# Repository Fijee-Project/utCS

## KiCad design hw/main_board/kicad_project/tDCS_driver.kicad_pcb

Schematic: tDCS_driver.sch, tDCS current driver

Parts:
P14, P15: CONN_5X2
P16: CONN_3X2
P17, P18: CONN_2X2
SCREW1, SCREW2, SCREW3, SCREW4: CONN_1

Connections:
/MUXC0: P14.9, P15.2; also elsewhere on the board
/MUXC1: P14.7, P15.4; also elsewhere on the board
/MUXC2: P14.5, P15.6; also elsewhere on the board
/MUXC3: P14.3, P15.8; also elsewhere on the board
/MUXC4: P14.1, P15.10; also elsewhere on the board
/MUXCOM0: P16.1, P16.6; also elsewhere on the board
/MUXCOM1: P16.3, P16.4; also elsewhere on the board
/MUXCOM2: P16.2, P16.5; also elsewhere on the board
/MUXD0: P14.10, P15.1; also elsewhere on the board
/MUXD1: P14.8, P15.3; also elsewhere on the board
/MUXD2: P14.6, P15.5; also elsewhere on the board
/MUXD3: P14.4, P15.7; also elsewhere on the board
/MUXD4: P14.2, P15.9; also elsewhere on the board
/powergen/MUXVSS: P18.1, P18.2; also elsewhere on the board
AGND: P17.1, P17.2, P17.3, P17.4; also elsewhere on the board
DVDD_2V5: P18.3, P18.4; also elsewhere on the board

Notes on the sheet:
A0-4 for the input/output mux boards

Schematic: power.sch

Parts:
P4: CONN_3X2

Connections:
/powergen/MUXVSS: P4.2; also elsewhere on the board
AGND: P4.4; also elsewhere on the board
AVDD: P4.5; also elsewhere on the board
AVSS: P4.6; also elsewhere on the board
DVDD_2V5: P4.1; also elsewhere on the board

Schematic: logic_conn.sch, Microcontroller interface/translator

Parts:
C37, C38, C41, C42: 0.1uF; 0603
P6: CONN_25X2
U8, U9: MAX3002; TSSOP_20

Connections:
/Clock/CLK_TWI0: P6.1; also elsewhere on the board
/Clock/CLK_TWI1: P6.2; also elsewhere on the board
/CurrentSource/GAIN_BUS0: P6.14; also elsewhere on the board
/CurrentSource/GAIN_BUS1: P6.10; also elsewhere on the board
/CurrentSource/GAIN_BUS2: P6.11; also elsewhere on the board
/CurrentSource/GAIN_BUS3: P6.12; also elsewhere on the board
/CurrentSource/GAIN_BUS4: P6.13; also elsewhere on the board
/CurrentSource/RNG_0: P6.23; also elsewhere on the board
/CurrentSource/RNG_1: P6.22; also elsewhere on the board
/CurrentSource/RNG_2: P6.21; also elsewhere on the board
/CurrentSource/RNG_3: P6.20; also elsewhere on the board
/DDS/DDS_BUS0: P6.7; also elsewhere on the board
/DDS/DDS_BUS1: P6.8; also elsewhere on the board
/DDS/DDS_BUS2: P6.9; also elsewhere on the board
/DDS/DDS_BUS3: P6.3; also elsewhere on the board
/DDS/DDS_BUS4: P6.4; also elsewhere on the board
/DDS/DDS_BUS5: P6.5; also elsewhere on the board
/DDS/DDS_BUS6: P6.6; also elsewhere on the board
/LogicTranslators/IN_MUX0: P6.26; also elsewhere on the board
/LogicTranslators/IN_MUX1: P6.27; also elsewhere on the board
/LogicTranslators/IN_MUX2: P6.24; also elsewhere on the board
/LogicTranslators/IN_MUX3: P6.25; also elsewhere on the board
/LogicTranslators/OUT_MUX0: P6.36; also elsewhere on the board
/LogicTranslators/OUT_MUX1: P6.37; also elsewhere on the board
/LogicTranslators/OUT_MUX2: P6.38; also elsewhere on the board
/LogicTranslators/OUT_MUX3: P6.39; also elsewhere on the board
/LogicTranslators/UCOUT14: P6.15, U8.20 (io-Vcc1)
/LogicTranslators/UCOUT15: P6.16, U8.18 (io-Vcc2)
/LogicTranslators/UCOUT16: P6.17, U8.17 (io-Vcc3)
/LogicTranslators/UCOUT17: P6.18, U8.16 (io-Vcc4)
/LogicTranslators/UCOUT18: P6.19, U8.15 (io-Vcc5)
/LogicTranslators/UCOUT27: P6.28, U9.20 (io-Vcc1)
/LogicTranslators/UCOUT28: P6.29, U9.18 (io-Vcc2)
/LogicTranslators/UCOUT29: P6.30, U9.17 (io-Vcc3)
/LogicTranslators/UCOUT30: P6.31, U9.16 (io-Vcc4)
/LogicTranslators/UCOUT31: P6.32, U9.15 (io-Vcc5)
/LogicTranslators/UCOUT32: P6.33, U9.14 (io-Vcc6)
/LogicTranslators/UCOUT33: P6.34, U9.13 (io-Vcc7)
/LogicTranslators/UCOUT34: P6.35, U9.12 (io-Vcc8)
/LogicTranslators/UCOUT39: P6.40
/LogicTranslators/UCOUT40: P6.41
/LogicTranslators/UCOUT41: P6.42
/LogicTranslators/UCOUT42: P6.43
/LogicTranslators/UCOUT43: P6.44
/LogicTranslators/UCOUT44: P6.45
/LogicTranslators/UCOUT45: P6.46
/LogicTranslators/UCOUT46: P6.47
/LogicTranslators/UCOUT47: P6.48
/LogicTranslators/UCOUT48: P6.49
/LogicTranslators/UCOUT49: P6.50
/MUXC0: U9.6 (io-Vl5); also elsewhere on the board
/MUXC1: U9.5 (io-Vl4); also elsewhere on the board
/MUXC2: U9.4 (io-Vl3); also elsewhere on the board
/MUXC3: U9.3 (io-Vl2); also elsewhere on the board
/MUXC4: U9.1 (io-Vl1); also elsewhere on the board
/MUXCOM0: U9.7 (io-Vl6); also elsewhere on the board
/MUXCOM1: U9.9 (io-Vl8); also elsewhere on the board
/MUXCOM2: U9.8 (io-Vl7); also elsewhere on the board
/MUXD0: U8.1 (io-Vl1); also elsewhere on the board
/MUXD1: U8.3 (io-Vl2); also elsewhere on the board
/MUXD2: U8.4 (io-Vl3); also elsewhere on the board
/MUXD3: U8.5 (io-Vl4); also elsewhere on the board
/MUXD4: U8.6 (io-Vl5); also elsewhere on the board
AGND: C37.2, C38.2, C41.2, C42.2, U9.11 (GND); also elsewhere on the board
DVDD_2V5: C37.1, C38.1, U8.2 (Vl), U9.2 (Vl); also elsewhere on the board

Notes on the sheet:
Does not need 2wire pullups, pulldowns needed for default on sleep/pselect/fselect (bit 6,7,9)

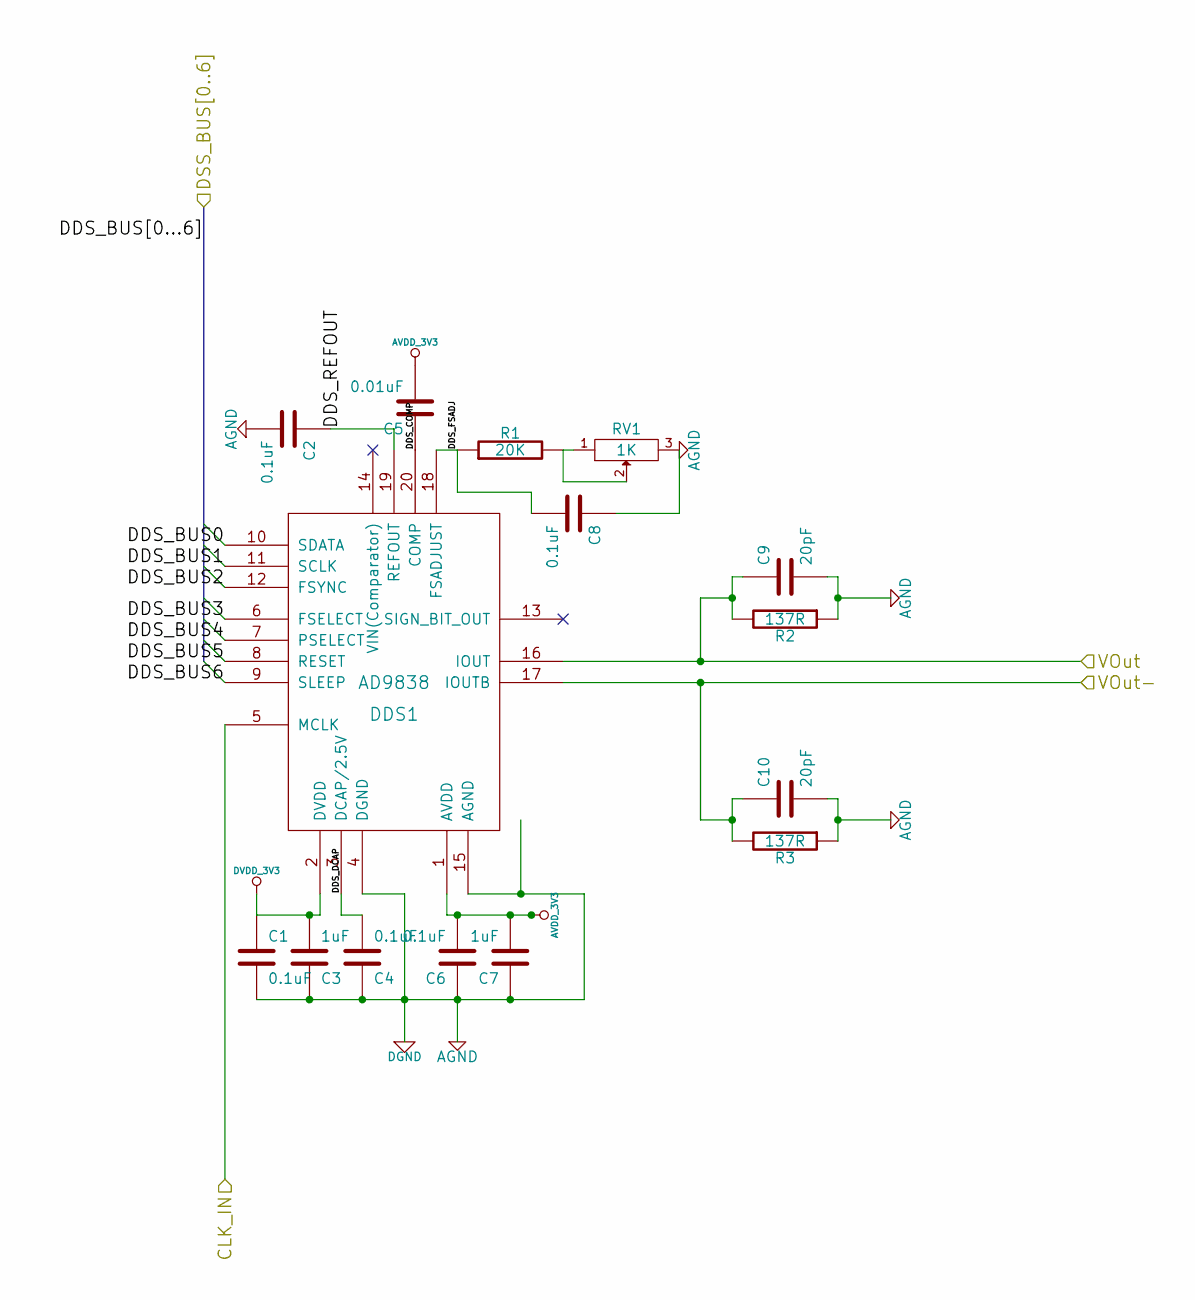
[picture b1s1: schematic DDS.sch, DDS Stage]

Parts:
C1, C2, C4, C6, C8: 0.1uF; 0603
C3, C7: 1uF; 0603
C5: 0.01uF; 0603
C9, C10: 20pF; 0603
DDS1: AD9838; LFCSP20_WQ
R1: 20K; 0603
R2, R3: 137R; 0603
RV1: 1K; 3224X

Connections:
/DDS/CLK_IN: DDS1.5 (MCLK); also elsewhere on the board
/DDS/DDS_BUS0: DDS1.10 (SDATA); also elsewhere on the board
/DDS/DDS_BUS1: DDS1.11 (SCLK); also elsewhere on the board
/DDS/DDS_BUS2: DDS1.12 (FSYNC); also elsewhere on the board
/DDS/DDS_BUS3: DDS1.6 (FSELECT); also elsewhere on the board
/DDS/DDS_BUS4: DDS1.7 (PSELECT); also elsewhere on the board
/DDS/DDS_BUS5: DDS1.8 (RESET); also elsewhere on the board
/DDS/DDS_BUS6: DDS1.9 (SLEEP); also elsewhere on the board
/DDS/DDS_COMP: C5.1, DDS1.20 (COMP)
/DDS/DDS_DCAP: C4.2, DDS1.3 (DCAP/2.5V)
/DDS/DDS_FSADJ: C8.2, DDS1.18 (FSADJUST), R1.1
/DDS/DDS_REFOUT: C2.1, DDS1.19 (REFOUT)
/DDS/VOut: C9.1, DDS1.16 (IOUT), R2.2; also elsewhere on the board
/DDS/VOut-: C10.1, DDS1.17 (IOUTB), R3.2; also elsewhere on the board
AGND: C1.2, C2.2, C3.1, C4.1, C6.1, C7.1, C8.1, C9.2, C10.2, DDS1.4 (DGND), DDS1.15 (AGND), DDS1.EP, R2.1, R3.1, RV1.3; also elsewhere on the board
unnamed: R1.2, RV1.1, RV1.2

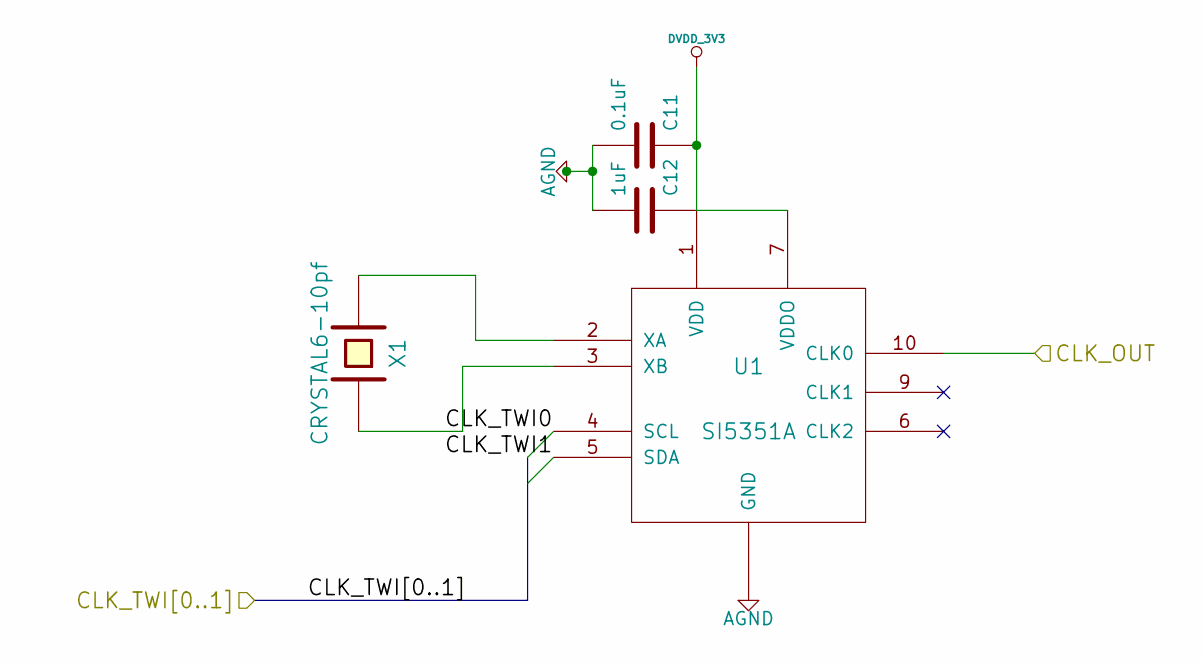
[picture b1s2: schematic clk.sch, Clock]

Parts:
C11: 0.1uF; 0603
C12: 1uF; 0603
U1: SI5351A; QSOP_16
X1: CRYSTAL6-10pf; ECX_53B

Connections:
/Clock/CLK_TWI0: U1.4 (SCL); also elsewhere on the board
/Clock/CLK_TWI1: U1.5 (SDA); also elsewhere on the board
/DDS/CLK_IN: U1.10 (CLK0); also elsewhere on the board
AGND: C11.2, C12.2, U1.8, U1.~ (GND); also elsewhere on the board
unnamed: U1.2 (XA), X1.2
unnamed: U1.3 (XB), X1.1

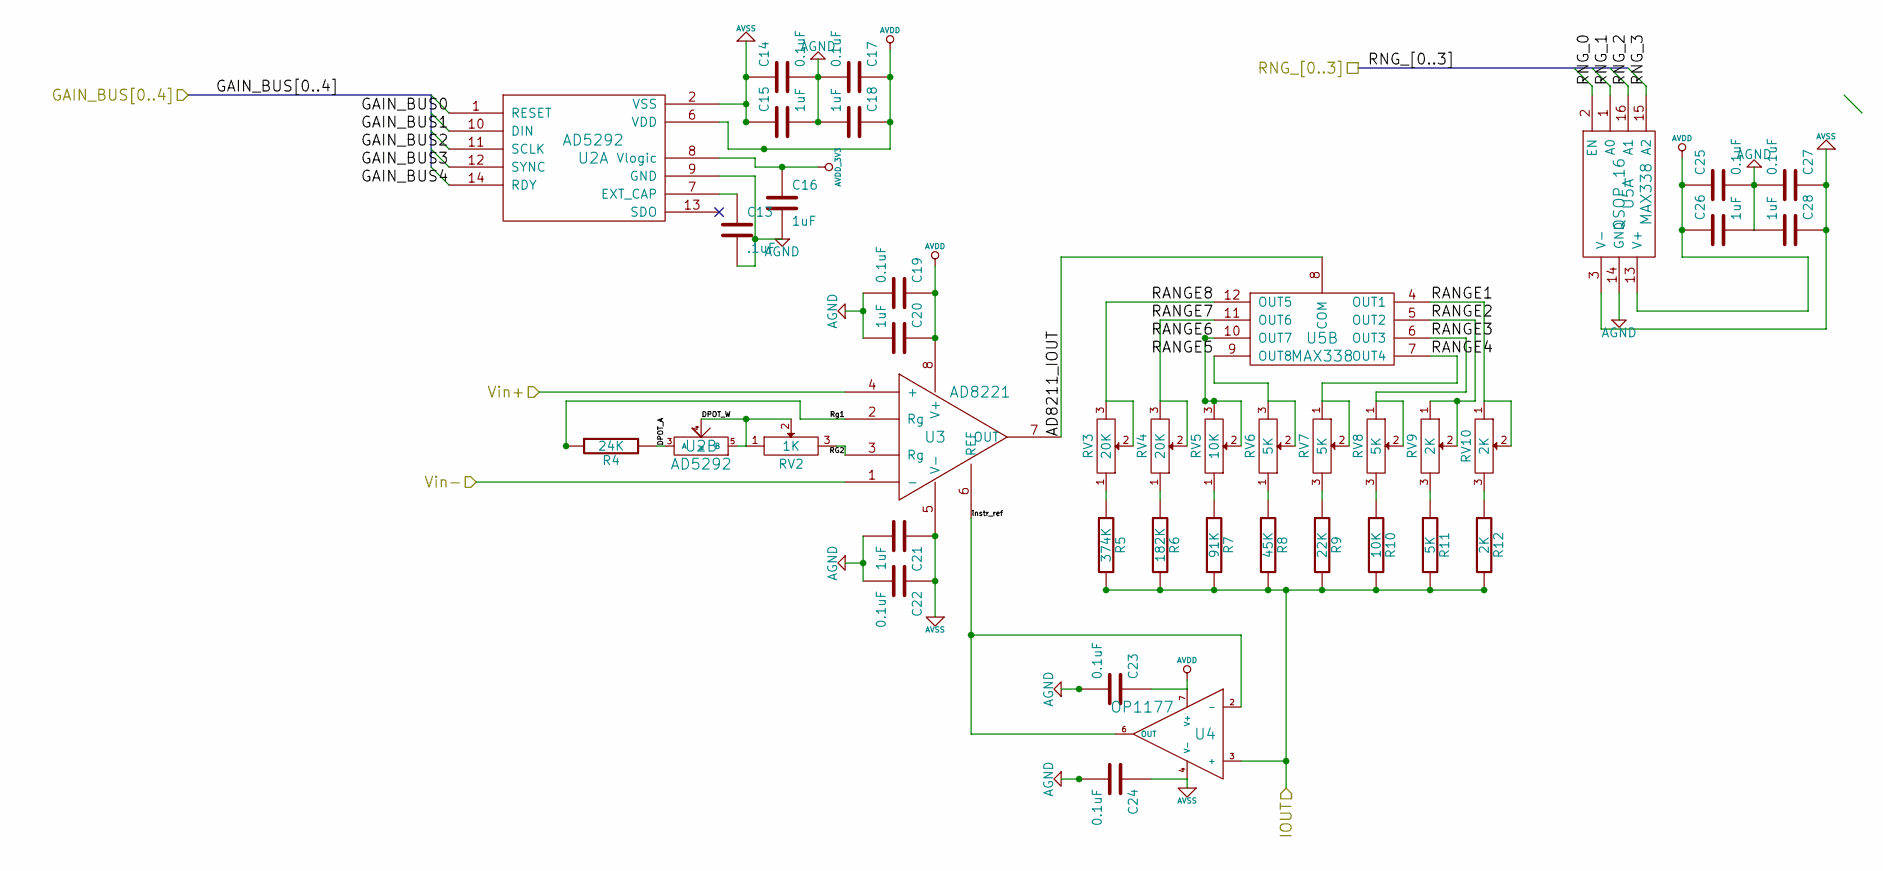
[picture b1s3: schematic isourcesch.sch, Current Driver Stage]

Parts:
C13: .1uF; 0603
C14, C17, C19, C22, C23, C24, C25, C27: 0.1uF; 0603
C15, C16, C18, C20, C21, C26, C28: 1uF; 0603
R4: 24K; 0603
R5: 374K; 0603
R6: 182K; 0603
R7: 91K; 0603
R8: 45K; 0603
R9: 22K; 0603
R10: 10K; 0603
R11: 5K; 0603
R12: 2K; 0603
RV2: 1K; 3224X
RV3, RV4: 20K; 3224X
RV5: 10K; 3224X
RV6, RV7, RV8: 5K; 3224X
RV9, RV10: 2K; 3224X
U2: AD5292; MSOP-10
U3: AD8221; TSSOP_14
U4: OP1177; MSOP_8
U5: MAX338; QSOP_16

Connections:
/CurrentSource/AD8211_IOUT: U3.7 (OUT), U5.8 (COM)
/CurrentSource/DPOT_A: R4.2, U2.3 (A)
/CurrentSource/DPOT_W: RV2.1, RV2.2, U2.4 (W), U2.5 (B)
/CurrentSource/GAIN_BUS0: U2.1 (RESET); also elsewhere on the board
/CurrentSource/GAIN_BUS1: U2.10 (DIN); also elsewhere on the board
/CurrentSource/GAIN_BUS2: U2.11 (SCLK); also elsewhere on the board
/CurrentSource/GAIN_BUS3: U2.12 (SYNC); also elsewhere on the board
/CurrentSource/GAIN_BUS4: U2.14 (RDY); also elsewhere on the board
/CurrentSource/IOUT: R5.2, R6.2, R7.2, R8.2, R9.2, R10.2, R11.2, R12.2, U4.3 (+); also elsewhere on the board
/CurrentSource/RANGE1: RV10.1, RV10.2, U5.4 (OUT1)
/CurrentSource/RANGE2: RV9.1, RV9.2, U5.5 (OUT2)
/CurrentSource/RANGE3: RV8.1, RV8.2, U5.6 (OUT3)
/CurrentSource/RANGE4: RV7.1, RV7.2, U5.7 (OUT4)
/CurrentSource/RANGE5: RV6.2, RV6.3, U5.9 (OUT8)
/CurrentSource/RANGE6: RV5.2, RV5.3, U5.10 (OUT7)
/CurrentSource/RANGE7: RV4.2, RV4.3, U5.11 (OUT6)
/CurrentSource/RANGE8: RV3.2, RV3.3, U5.12 (OUT5)
/CurrentSource/RG2: RV2.3, U3.3 (Rg)
/CurrentSource/RNG_0: U5.2 (EN); also elsewhere on the board
/CurrentSource/RNG_1: U5.1 (A0); also elsewhere on the board
/CurrentSource/RNG_2: U5.16 (A1); also elsewhere on the board
/CurrentSource/RNG_3: U5.15 (A2); also elsewhere on the board
/CurrentSource/Rg1: R4.1, U3.2 (Rg)
/CurrentSource/instr_ref: U3.6 (REF), U4.2 (-), U4.6 (OUT)
/DDS/VOut: U3.4 (+); also elsewhere on the board
/DDS/VOut-: U3.1 (-); also elsewhere on the board
AGND: C13.2, C14.2, C15.2, C16.2, C17.2, C18.2, C19.2, C20.2, C21.2, C22.2, C23.2, C24.2, C25.2, C26.2, C27.2, C28.2, U2.9 (GND), U5.14 (GND); also elsewhere on the board
AVDD: C17.1, C18.1, C19.1, C20.1, C23.1, C25.1, C26.1, U2.6 (VDD), U3.8 (V+), U4.7 (V+), U5.13 (V+); also elsewhere on the board
AVSS: C14.1, C15.1, C21.1, C22.1, C24.1, C27.1, C28.1, U2.2 (VSS), U3.5 (V-), U4.4 (V-), U5.3 (V-); also elsewhere on the board
unnamed: R9.1, RV7.3
unnamed: R8.1, RV6.1
unnamed: R7.1, RV5.1
unnamed: R6.1, RV4.1
unnamed: R11.1, RV9.3
unnamed: R12.1, RV10.3
unnamed: R10.1, RV8.3
unnamed: C13.1, U2.7 (EXT_CAP)
unnamed: R5.1, RV3.1

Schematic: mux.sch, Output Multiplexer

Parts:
C29, C31, C33, C43: 0.1uF; 0603
C30, C32, C34, C44: 1uF; 0603
P5, P7, P8, P9, P10, P11, P12, P13: CONN_2
U6, U7: MAX338; QSOP_16

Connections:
/CurrentSource/IOUT: U6.8 (COM); also elsewhere on the board
/LogicTranslators/IN_MUX0: U6.2 (EN); also elsewhere on the board
/LogicTranslators/IN_MUX1: U6.1 (A0); also elsewhere on the board
/LogicTranslators/IN_MUX2: U6.16 (A1); also elsewhere on the board
/LogicTranslators/IN_MUX3: U6.15 (A2); also elsewhere on the board
/LogicTranslators/OUT_MUX0: U7.2 (EN); also elsewhere on the board
/LogicTranslators/OUT_MUX1: U7.1 (A0); also elsewhere on the board
/LogicTranslators/OUT_MUX2: U7.16 (A1); also elsewhere on the board
/LogicTranslators/OUT_MUX3: U7.15 (A2); also elsewhere on the board
/OutputMultiplexer/MUXA0: P5.1, U6.4 (OUT1)
/OutputMultiplexer/MUXA1: P7.1, U6.5 (OUT2)
/OutputMultiplexer/MUXA2: P9.1, U6.6 (OUT3)
/OutputMultiplexer/MUXA3: P10.1, U6.7 (OUT4)
/OutputMultiplexer/MUXA4: P11.2, U6.12 (OUT5)
/OutputMultiplexer/MUXA5: P12.2, U6.11 (OUT6)
/OutputMultiplexer/MUXA6: P8.2, U6.10 (OUT7)
/OutputMultiplexer/MUXA7: P13.2, U6.9 (OUT8)
/OutputMultiplexer/MUXB0: P5.2, U7.7 (OUT4)
/OutputMultiplexer/MUXB1: P7.2, U7.6 (OUT3)
/OutputMultiplexer/MUXB2: P9.2, U7.5 (OUT2)
/OutputMultiplexer/MUXB3: P10.2, U7.4 (OUT1)
/OutputMultiplexer/MUXB4: P11.1, U7.9 (OUT8)
/OutputMultiplexer/MUXB5: P12.1, U7.10 (OUT7)
/OutputMultiplexer/MUXB6: P8.1, U7.11 (OUT6)
/OutputMultiplexer/MUXB7: P13.1, U7.12 (OUT5)
AGND: C29.2, C30.2, C31.2, C32.2, C33.2, C34.2, C43.2, C44.2, U6.14 (GND), U7.8 (COM), U7.14 (GND); also elsewhere on the board
AVDD: C29.1, C30.1, C33.1, C34.1, U6.13 (V+), U7.13 (V+); also elsewhere on the board
AVSS: C31.1, C32.1, C43.1, C44.1, U6.3 (V-), U7.3 (V-); also elsewhere on the board

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
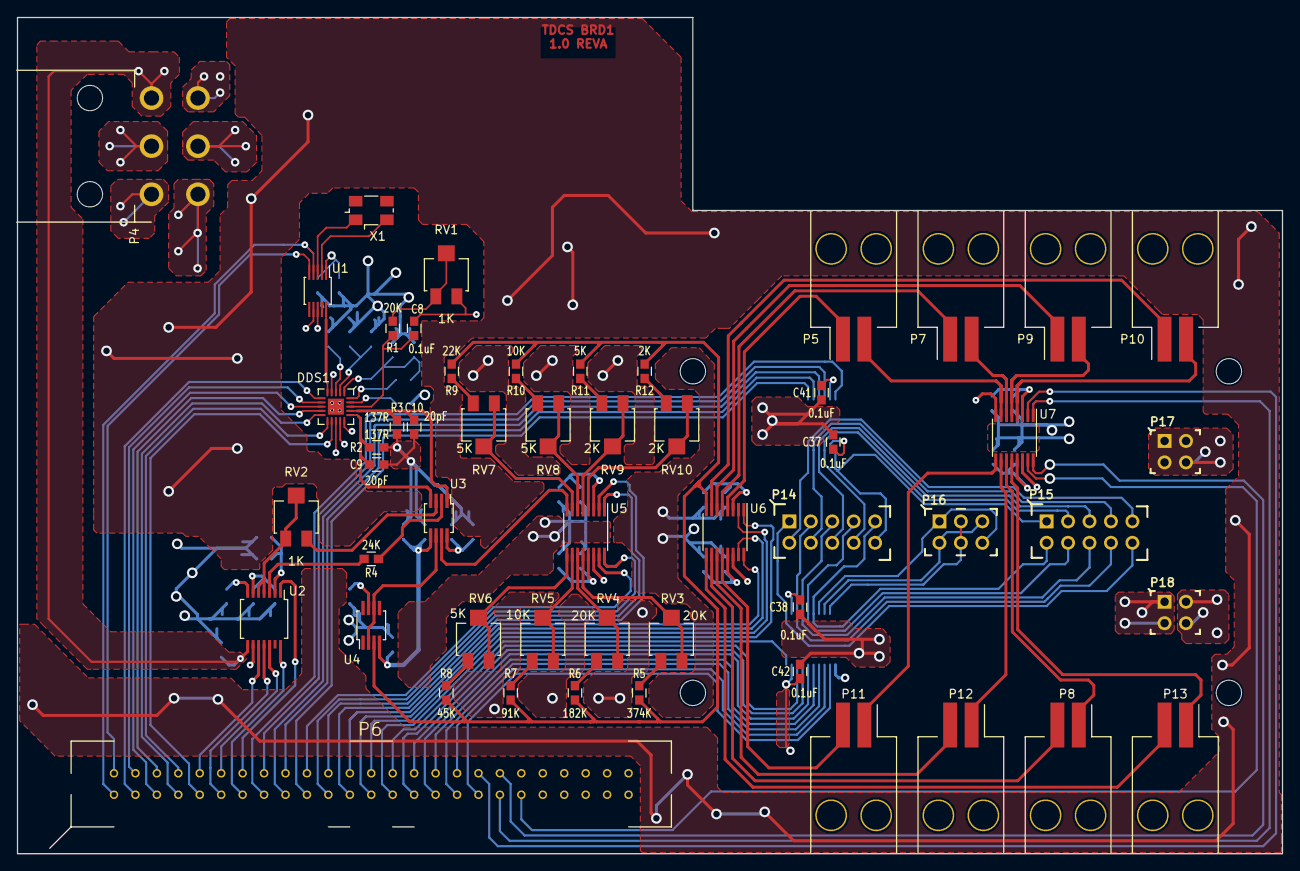
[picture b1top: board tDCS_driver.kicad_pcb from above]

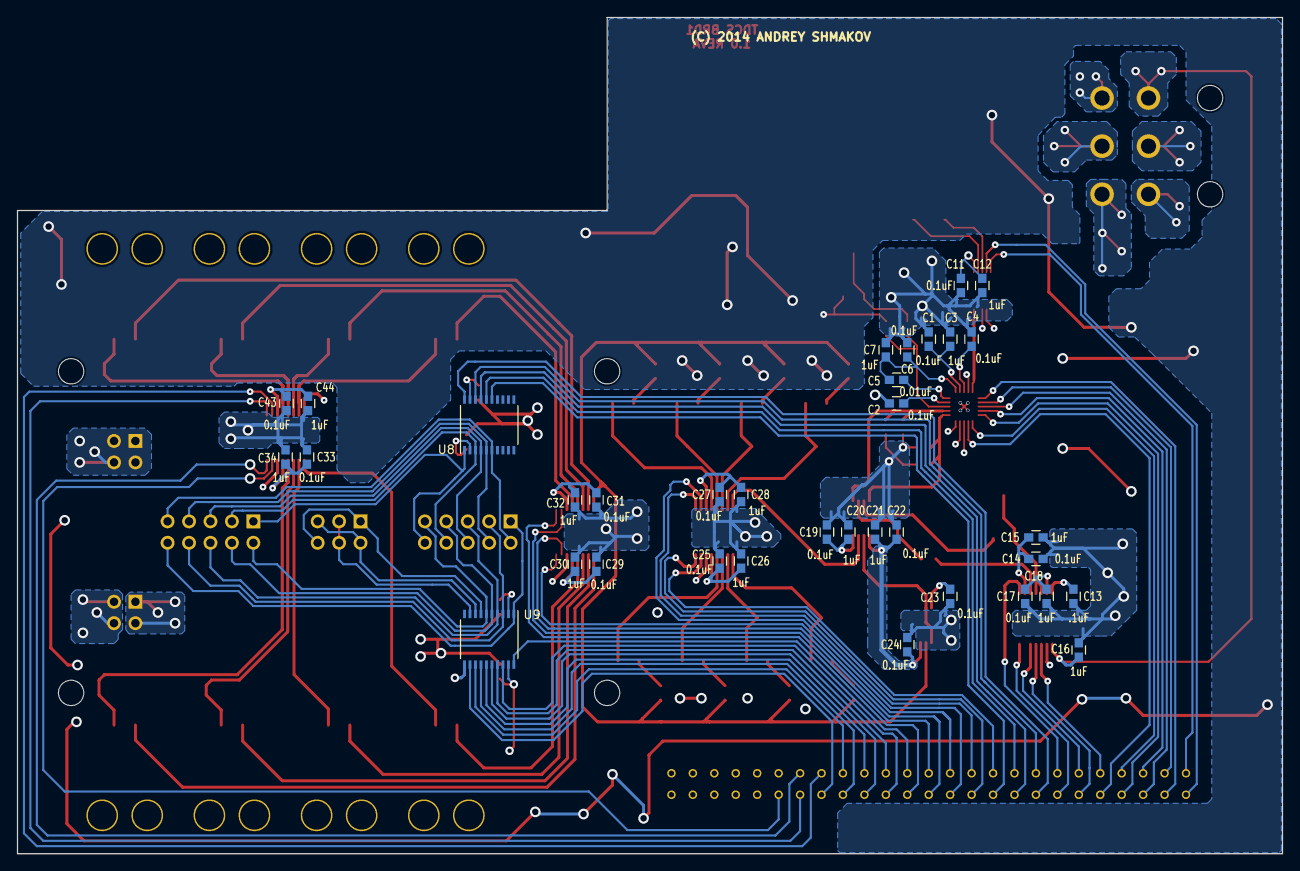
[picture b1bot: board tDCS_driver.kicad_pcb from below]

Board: 4 copper layers, 149.9 x 99.1 mm, 92 parts (35 on the bottom side), 108 nets.

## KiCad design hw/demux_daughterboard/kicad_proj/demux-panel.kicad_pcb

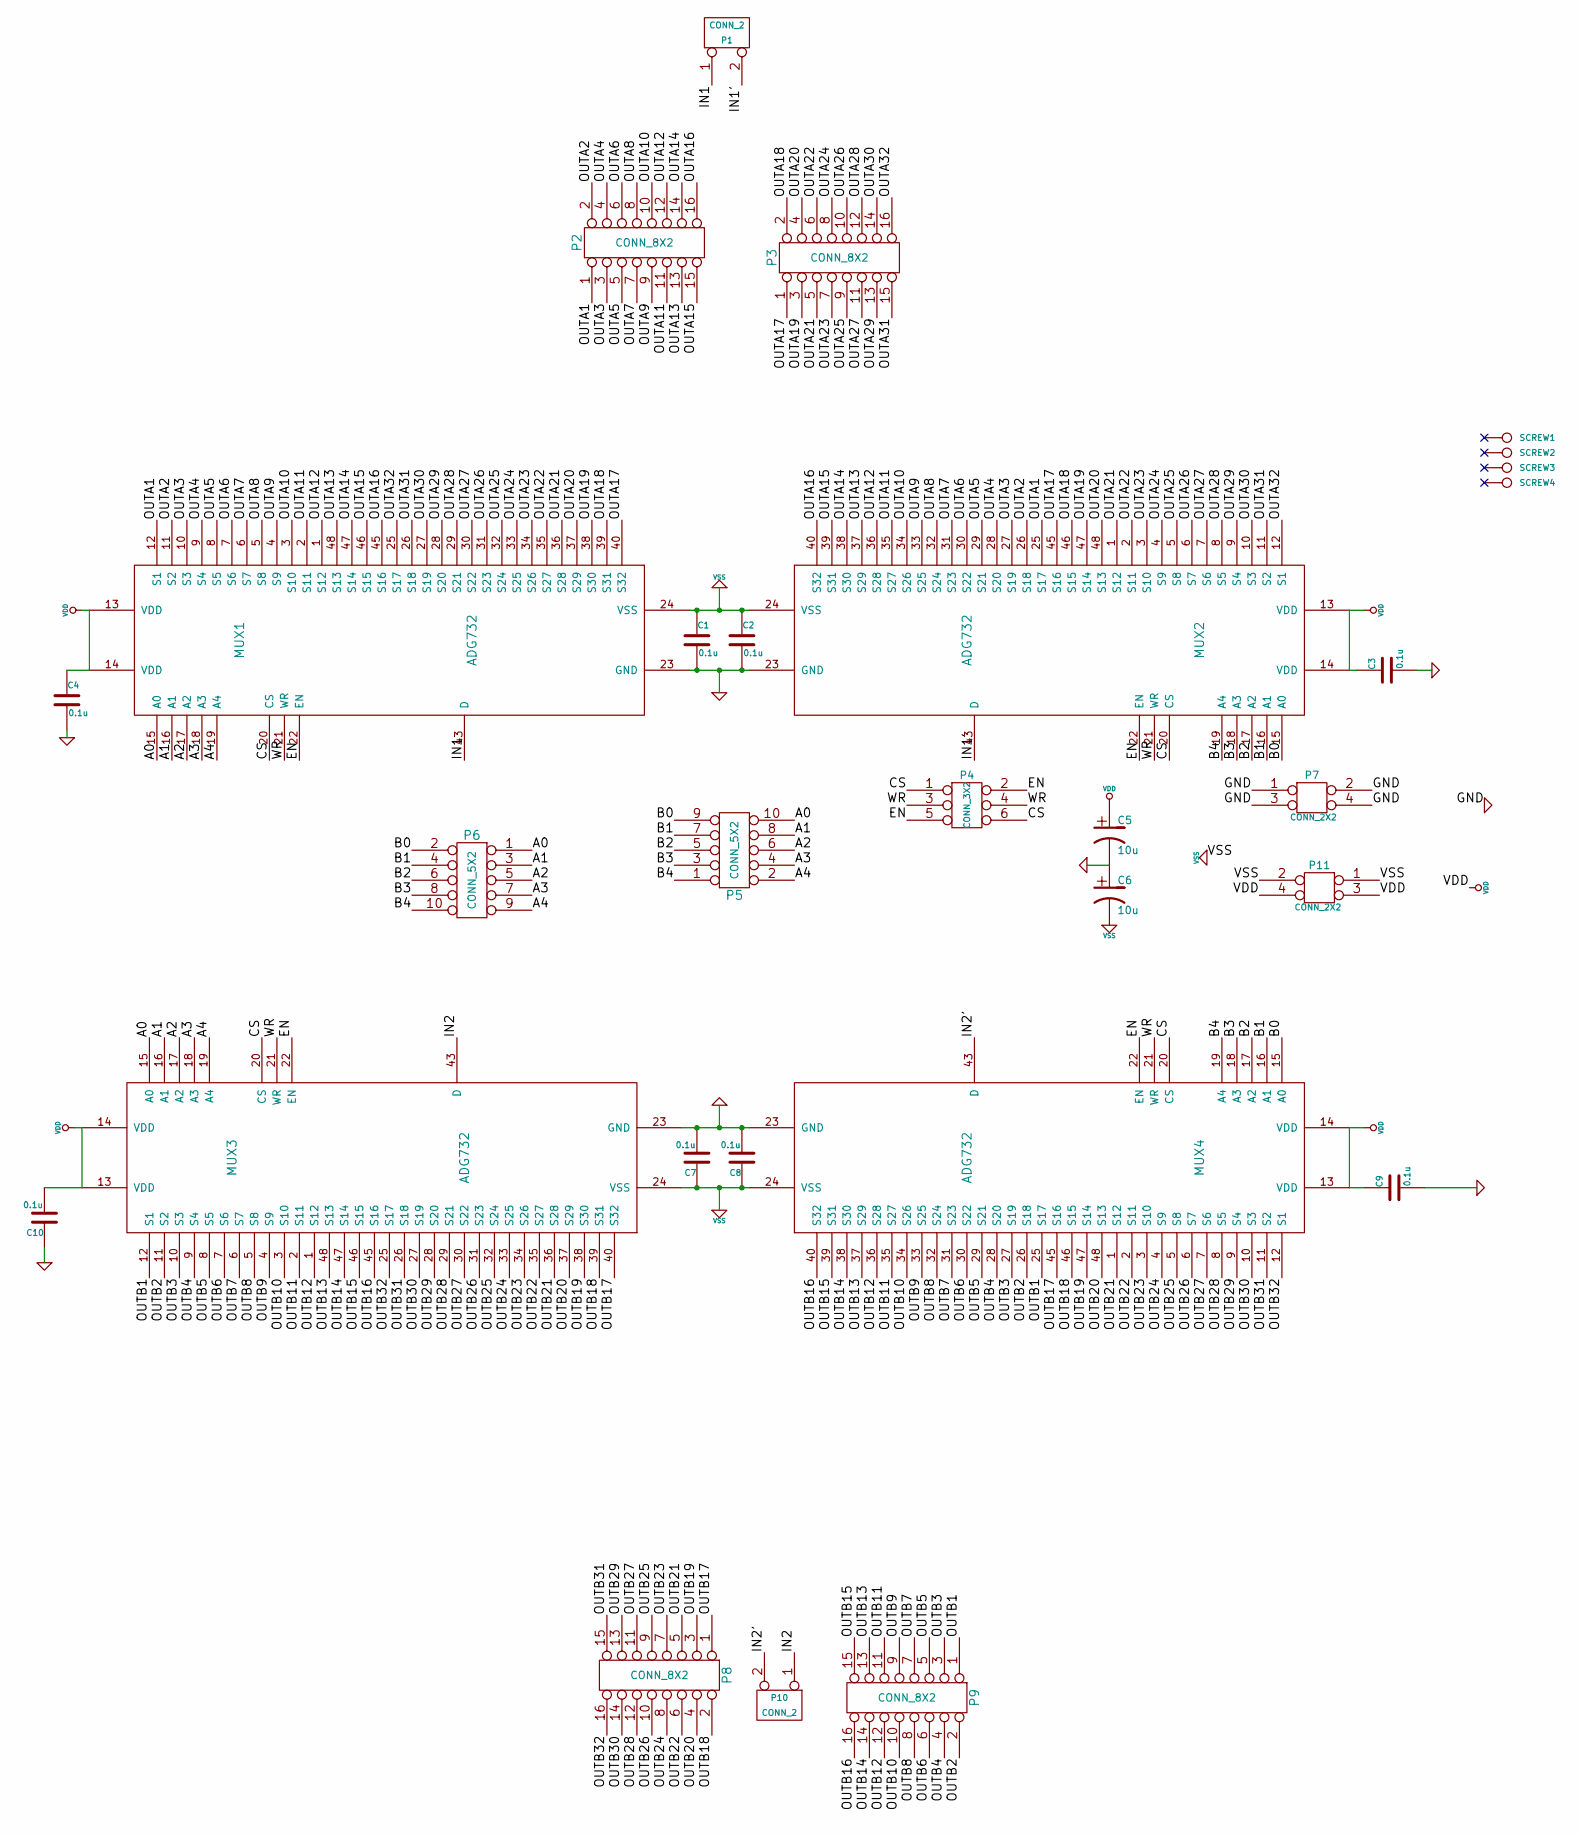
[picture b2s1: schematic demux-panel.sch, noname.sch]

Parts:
C1, C2, C3, C4, C7, C8, C9, C10: 0.1u
C5, C6: 10u
MUX1, MUX2, MUX3, MUX4: ADG732
P1, P10: CONN_2
P2, P3, P8, P9: CONN_8X2
P4: CONN_3X2
P5, P6: CONN_5X2
P7, P11: CONN_2X2
SCREW1, SCREW2, SCREW3, SCREW4: CONN_1

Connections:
/A0: MUX1.15 (A0), MUX3.15 (A0), P5.10, P6.1
/A1: MUX1.16 (A1), MUX3.16 (A1), P5.8, P6.3
/A2: MUX1.17 (A2), MUX3.17 (A2), P5.6, P6.5
/A3: MUX1.18 (A3), MUX3.18 (A3), P5.4, P6.7
/A4: MUX1.19 (A4), MUX3.19 (A4), P5.2, P6.9
/B0: MUX2.15 (A0), MUX4.15 (A0), P5.9, P6.2
/B1: MUX2.16 (A1), MUX4.16 (A1), P5.7, P6.4
/B2: MUX2.17 (A2), MUX4.17 (A2), P5.5, P6.6
/B3: MUX2.18 (A3), MUX4.18 (A3), P5.3, P6.8
/B4: MUX2.19 (A4), MUX4.19 (A4), P5.1, P6.10
/CS: MUX1.20 (CS), MUX2.20 (CS), MUX3.20 (CS), MUX4.20 (CS), P4.1, P4.6
/EN: MUX1.22 (EN), MUX2.22 (EN), MUX3.22 (EN), MUX4.22 (EN), P4.2, P4.5
/IN1: MUX1.43 (D), P1.1
/IN1': MUX2.43 (D), P1.2 (PM)
/IN2: MUX3.43 (D), P10.1
/IN2': MUX4.43 (D), P10.2 (PM)
/OUTA1: MUX1.12 (S1), MUX2.25 (S17), P2.1
/OUTA2: MUX1.11 (S2), MUX2.26 (S18), P2.2
/OUTA3: MUX1.10 (S3), MUX2.27 (S19), P2.3
/OUTA4: MUX1.9 (S4), MUX2.28 (S20), P2.4
/OUTA5: MUX1.8 (S5), MUX2.29 (S21), P2.5
/OUTA6: MUX1.7 (S6), MUX2.30 (S22), P2.6
/OUTA7: MUX1.6 (S7), MUX2.31 (S23), P2.7
/OUTA8: MUX1.5 (S8), MUX2.32 (S24), P2.8
/OUTA9: MUX1.4 (S9), MUX2.33 (S25), P2.9
/OUTA10: MUX1.3 (S10), MUX2.34 (S26), P2.10
/OUTA11: MUX1.2 (S11), MUX2.35 (S27), P2.11
/OUTA12: MUX1.1 (S12), MUX2.36 (S28), P2.12
/OUTA13: MUX1.48 (S13), MUX2.37 (S29), P2.13
/OUTA14: MUX1.47 (S14), MUX2.38 (S30), P2.14
/OUTA15: MUX1.46 (S15), MUX2.39 (S31), P2.15
/OUTA16: MUX1.45 (S16), MUX2.40 (S32), P2.16
/OUTA17: MUX1.40 (S32), MUX2.45 (S16), P3.1
/OUTA18: MUX1.39 (S31), MUX2.46 (S15), P3.2
/OUTA19: MUX1.38 (S30), MUX2.47 (S14), P3.3
/OUTA20: MUX1.37 (S29), MUX2.48 (S13), P3.4
/OUTA21: MUX1.36 (S28), MUX2.1 (S12), P3.5
/OUTA22: MUX1.35 (S27), MUX2.2 (S11), P3.6
/OUTA23: MUX1.34 (S26), MUX2.3 (S10), P3.7
/OUTA24: MUX1.33 (S25), MUX2.4 (S9), P3.8
/OUTA25: MUX1.32 (S24), MUX2.5 (S8), P3.9
/OUTA26: MUX1.31 (S23), MUX2.6 (S7), P3.10
/OUTA27: MUX1.30 (S22), MUX2.7 (S6), P3.11
/OUTA28: MUX1.29 (S21), MUX2.8 (S5), P3.12
/OUTA29: MUX1.28 (S20), MUX2.9 (S4), P3.13
/OUTA30: MUX1.27 (S19), MUX2.10 (S3), P3.14
/OUTA31: MUX1.26 (S18), MUX2.11 (S2), P3.15
/OUTA32: MUX1.25 (S17), MUX2.12 (S1), P3.16
/OUTB1: MUX3.12 (S1), MUX4.25 (S17), P9.1
/OUTB2: MUX3.11 (S2), MUX4.26 (S18), P9.2
/OUTB3: MUX3.10 (S3), MUX4.27 (S19), P9.3
/OUTB4: MUX3.9 (S4), MUX4.28 (S20), P9.4
/OUTB5: MUX3.8 (S5), MUX4.29 (S21), P9.5
/OUTB6: MUX3.7 (S6), MUX4.30 (S22), P9.6
/OUTB7: MUX3.6 (S7), MUX4.31 (S23), P9.7
/OUTB8: MUX3.5 (S8), MUX4.32 (S24), P9.8
/OUTB9: MUX3.4 (S9), MUX4.33 (S25), P9.9
/OUTB10: MUX3.3 (S10), MUX4.34 (S26), P9.10
/OUTB11: MUX3.2 (S11), MUX4.35 (S27), P9.11
/OUTB12: MUX3.1 (S12), MUX4.36 (S28), P9.12
/OUTB13: MUX3.48 (S13), MUX4.37 (S29), P9.13
/OUTB14: MUX3.47 (S14), MUX4.38 (S30), P9.14
/OUTB15: MUX3.46 (S15), MUX4.39 (S31), P9.15
/OUTB16: MUX3.45 (S16), MUX4.40 (S32), P9.16
/OUTB17: MUX3.40 (S32), MUX4.45 (S16), P8.1
/OUTB18: MUX3.39 (S31), MUX4.46 (S15), P8.2
/OUTB19: MUX3.38 (S30), MUX4.47 (S14), P8.3
/OUTB20: MUX3.37 (S29), MUX4.48 (S13), P8.4
/OUTB21: MUX3.36 (S28), MUX4.1 (S12), P8.5
/OUTB22: MUX3.35 (S27), MUX4.2 (S11), P8.6
/OUTB23: MUX3.34 (S26), MUX4.3 (S10), P8.7
/OUTB24: MUX3.33 (S25), MUX4.4 (S9), P8.8
/OUTB25: MUX3.32 (S24), MUX4.5 (S8), P8.9
/OUTB26: MUX3.31 (S23), MUX4.6 (S7), P8.10
/OUTB27: MUX3.30 (S22), MUX4.7 (S6), P8.11
/OUTB28: MUX3.29 (S21), MUX4.8 (S5), P8.12
/OUTB29: MUX3.28 (S20), MUX4.9 (S4), P8.13
/OUTB30: MUX3.27 (S19), MUX4.10 (S3), P8.14
/OUTB31: MUX3.26 (S18), MUX4.11 (S2), P8.15
/OUTB32: MUX3.25 (S17), MUX4.12 (S1), P8.16
/WR: MUX1.21 (WR), MUX2.21 (WR), MUX3.21 (WR), MUX4.21 (WR), P4.3, P4.4
GND: C1.2, C2.2, C3.2, C4.2, C5.2, C6.1, C7.2, C8.2, C9.2, C10.1, MUX1.23 (GND), MUX2.23 (GND), MUX3.23 (GND), MUX4.23 (GND), P7.1, P7.2, P7.3, P7.4
VDD: C3.1, C4.1, C5.1, C9.1, C10.2, MUX1.13 (VDD), MUX1.14 (VDD), MUX2.13 (VDD), MUX2.14 (VDD), MUX3.13 (VDD), MUX3.14 (VDD), MUX4.13 (VDD), MUX4.14 (VDD), P11.3, P11.4
VSS: C1.1, C2.1, C6.2, C7.1, C8.1, MUX1.24 (VSS), MUX2.24 (VSS), MUX3.24 (VSS), MUX4.24 (VSS), P11.1, P11.2

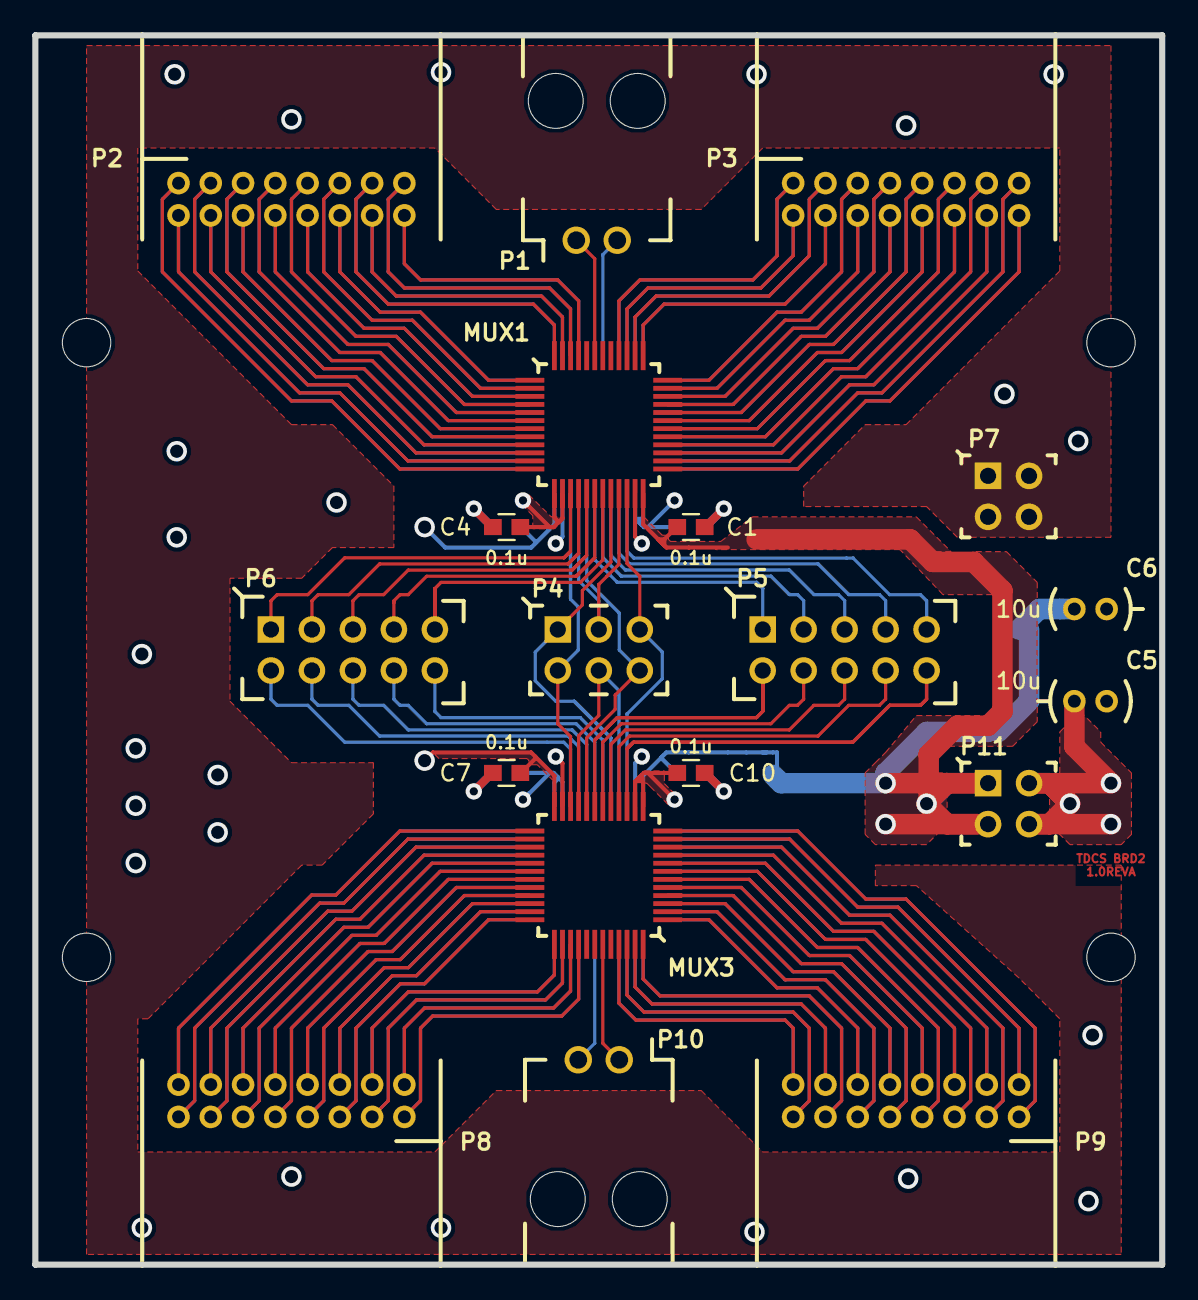
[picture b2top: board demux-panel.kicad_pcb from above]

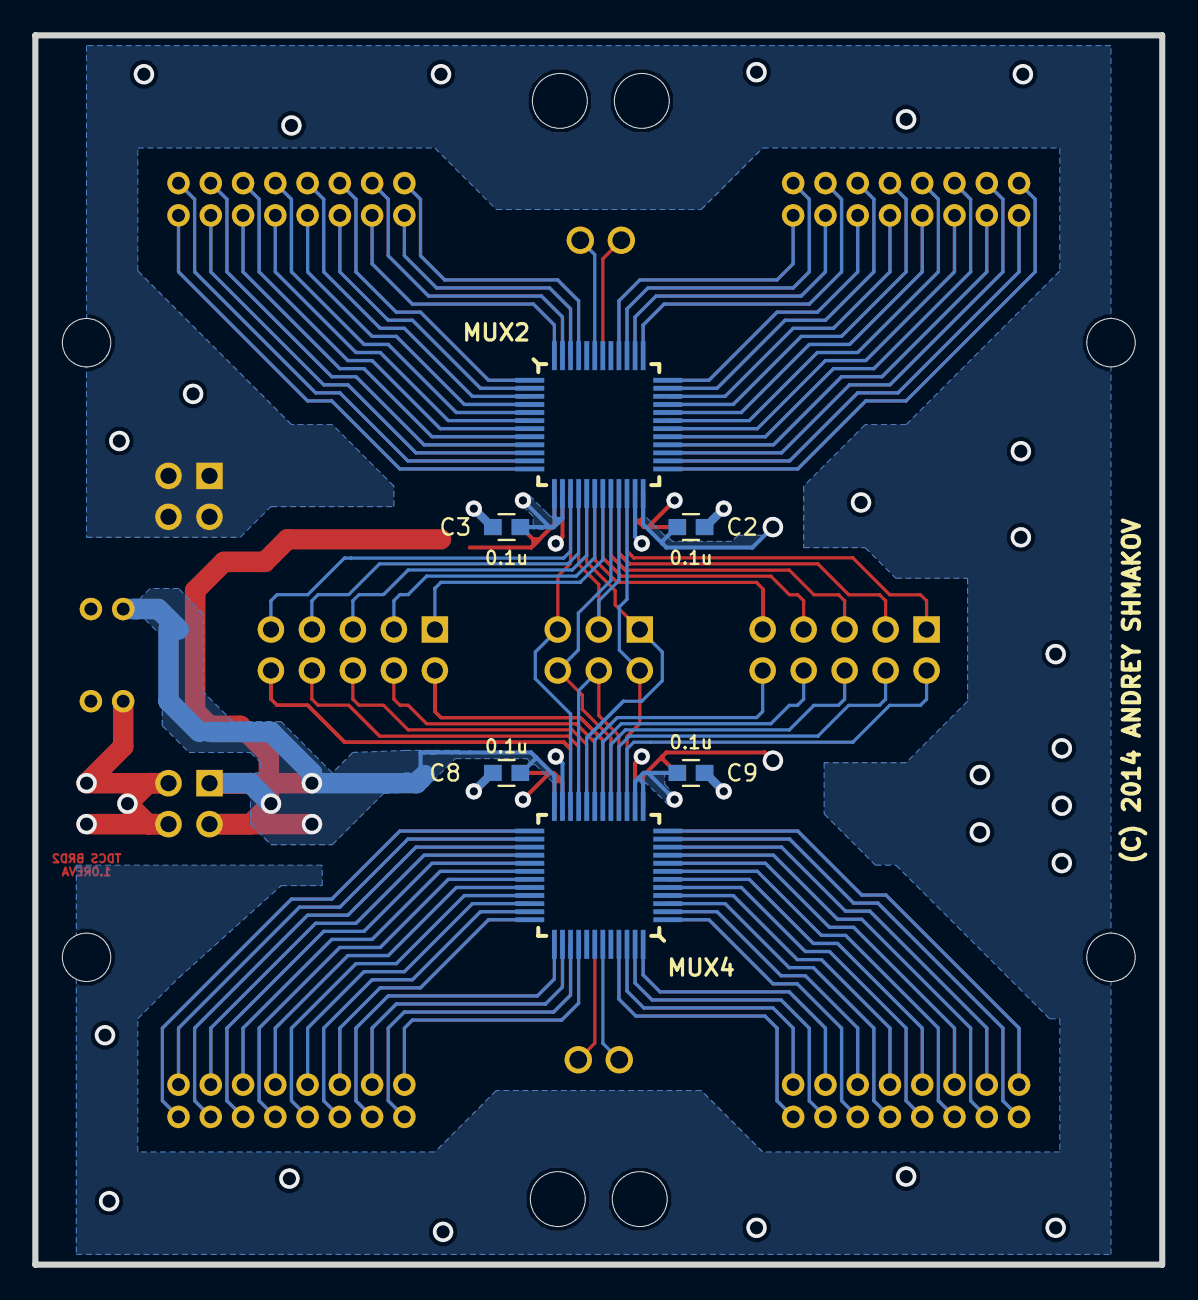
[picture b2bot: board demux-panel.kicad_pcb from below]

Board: 4 copper layers, 69.8 x 76.2 mm, 29 parts (6 on the bottom side), 84 nets.

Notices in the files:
hw/demux_daughterboard/kicad_proj/demux-panel.kicad_pcb:
Copyright Andrey Shmakov 2014
(C) 2014 ANDREY SHMAKOV
hw/main_board/kicad_project/DDS.sch:
Copyright 2014 Andrey Shmakov
